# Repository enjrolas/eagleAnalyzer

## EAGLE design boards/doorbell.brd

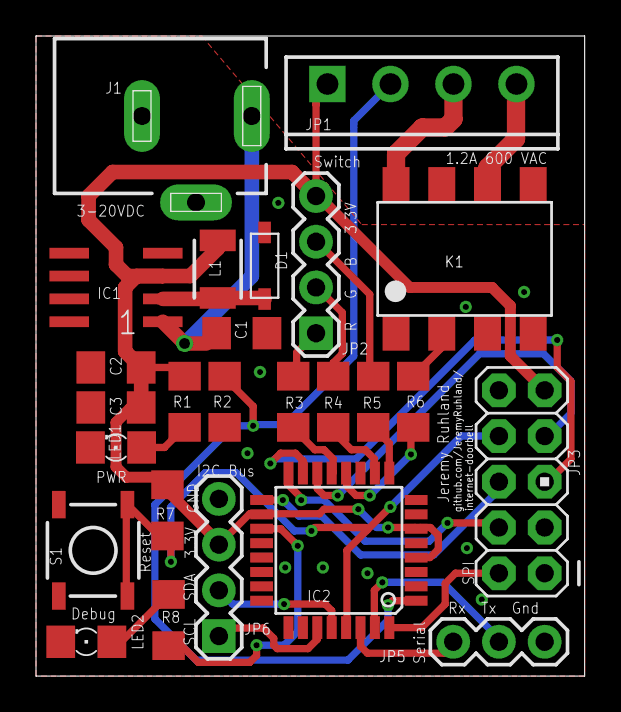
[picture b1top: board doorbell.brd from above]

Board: 2 copper layers, 30.5 x 35.6 mm, 25 parts (0 on the bottom side), 28 nets.

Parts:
C1, C2: 10uf; C1206
C3: 0.1uf; C1206
D1: SOD-123
IC1: AP1509; SOP-8
IC2: MEGA8-AI; TQFP32-08
J1: DCJ0202SILK; DCJ0202_SILK
JP1: SCREWTERMINAL-3.5MM-4_SILK
JP2: LED_header; 1X04
JP3: M05X2PTH; AVR_ICSP
JP5: 1X03
JP6: 1X04
K1: AQH213B; DIL08SMD
L1: 47uh; 1210
LED1, LED2: 1206
R1, R3, R4, R5, R6, R8: 160; R1206
R2, R7: 10k; R1206
S1: TACTILE_SWITCH_SMD

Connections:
3.3V: C2.1, C3.1, IC1.3, IC2.4, IC2.6, IC2.18, JP1.1, JP2.4, JP3.9, JP6.3, L1.2, R1.2, R7.2
B: IC2.13, R3.1
BELL: IC2.12, R6.2
BELL+: JP1.3, K1.8
BELL-: JP1.4, K1.6
CS: IC2.14, JP3.7
DBG: IC2.19, R8.2
G: IC2.10, R4.1
GND: C1.2, C2.2, C3.2, D1.A, IC1.4, IC1.5, IC1.6, IC1.7, IC1.8, IC2.3, IC2.5, IC2.21, J1.2, J1.3, JP3.10, JP5.3, JP6.4, K1.4, LED1.C, LED2.C, R2.1, S1.1, S1.2
INT0: IC2.32, JP3.2
MISO: IC2.16, JP3.4
MOSI: IC2.15, JP3.5
unnamed: K1.2, R6.1
unnamed: C1.1, IC1.1, J1.1
unnamed: D1.C, IC1.2, L1.1
unnamed: IC2.27, JP6.1
unnamed: IC2.28, JP6.2
unnamed: LED1.A, R1.1
unnamed: LED2.A, R8.1
unnamed: JP2.3, R5.2
unnamed: JP2.2, R4.2
unnamed: JP2.1, R3.2
R: IC2.9, R5.1
RST: IC2.29, JP3.8, R7.1, S1.3, S1.4
RX: IC2.30, JP5.1
SCK: IC2.17, JP3.6
SIG: IC2.1, JP1.2, R2.2
TX: IC2.31, JP5.2

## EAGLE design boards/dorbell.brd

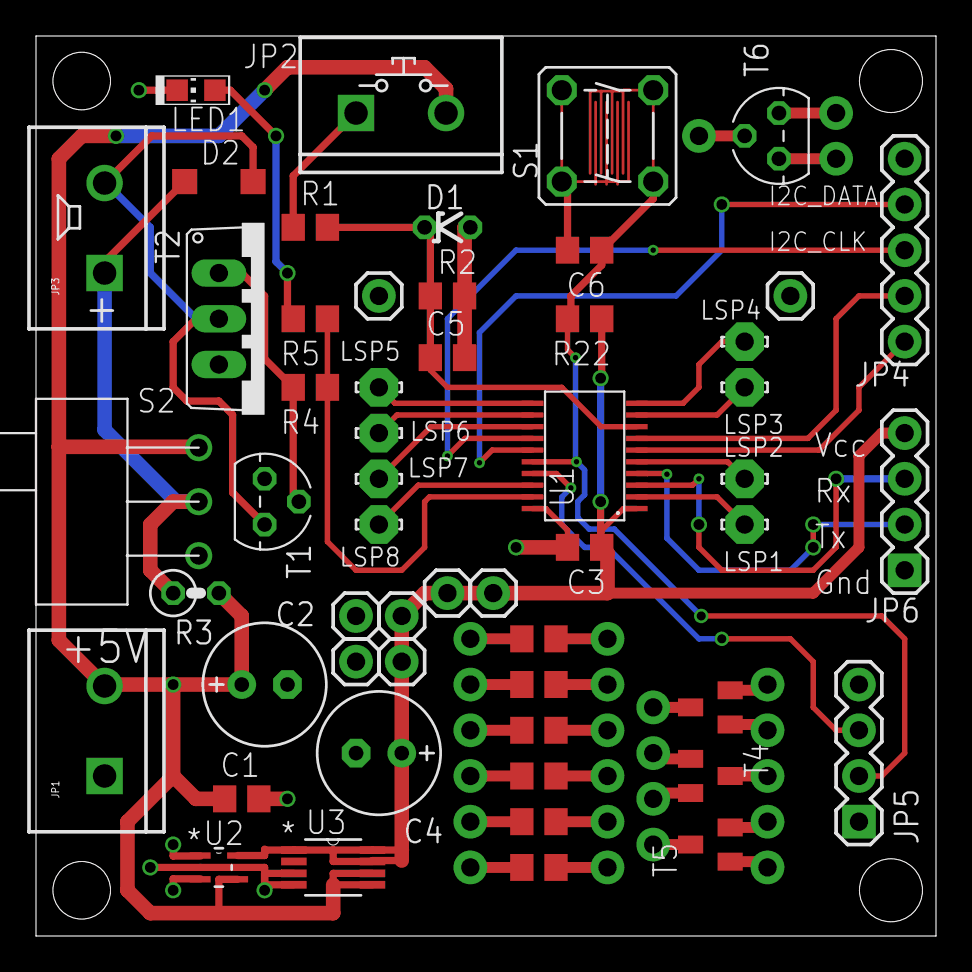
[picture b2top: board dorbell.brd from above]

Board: 2 copper layers, 50.0 x 50.0 mm, 78 parts (0 on the bottom side), 50 nets.

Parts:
C1, C3, C5, C6: C0805
C2, C4: E2,5-7
D1: 3.3V; ZDIO-2.5
D2: 1N4148; SOD123
JP1, JP2, JP3: T1; SCREWTERMINAL-5MM-2
JP4: 1X05
JP5, JP6: 1X04
JP7, JP8, JP9, JP10, JP11, JP12, JP13, JP14, JP15, JP16, JP17, JP18, JP19, JP20, JP21, JP22, JP23, JP24, JP25, JP26, JP27, JP28, JP29, JP30: M01SMDNS; 1X01NS
JP31, JP32, JP33, JP34, JP35, JP36, JP37, JP38: M01PTH; 1X01
LED1: GREEN; CHIP-LED0805
LSP1, LSP2, LSP3, LSP4, LSP5, LSP6, LSP7, LSP8: LSP10
R1, R4, R5: 470; R0805
R2, R6, R7, R8, R9, R10, R11: 4.7K; R0805
R3: 4.7K; 0207/2V
R22: 47K; R0805
S1: DTE6
S2: SWITCH_2DIR; SWITCH_SLIDE
T1: 2N3904; TO92
T2: BD537; TO220V
T3, T4, T5: SOT23-BEC
T6: TO92-E1
U1: G2XX3---PW20; PW20
U2: TPS71533_DCK_5; DCK5
U3: TPS77333; DGK8

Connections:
+5V: C1.1, C2.+, JP1.2, JP2.2, R3.2, S2.P$1, U2.4, U3.5, U3.6
BTN: C5.1, D1.C, R1.2, R2.2, U1.8
GND: C1.2, C2.-, C3.2, C4.-, C5.2, C6.2, D1.A, JP1.1, JP4.1, JP5.1, JP6.1, JP31.1, JP32.1, JP33.1, JP34.1, LED1.C, R2.1, S1.1, S1.2, T1.3, T2.3, U1.20, U2.2, U3.3, U3.4
I2C_CLK: JP4.3, U1.14
I2C_DATA: JP4.2, U1.15
unnamed: D2.A, JP3.2, T1.1, T2.2
unnamed: D2.C, JP3.1, R3.1, S2.P$2
unnamed: R4.2, T1.2, T2.1
unnamed: JP2.1, R1.1
unnamed: LED1.A, R5.2
unnamed: JP7.1, R6.2
unnamed: JP8.1, R6.1
unnamed: JP9.1, R7.2
unnamed: JP10.1, R7.1
unnamed: JP11.1, R8.2
unnamed: JP12.1, R8.1
unnamed: JP13.1, R9.2
unnamed: JP14.1, R9.1
unnamed: JP15.1, R10.2
unnamed: JP16.1, R10.1
unnamed: JP17.1, R11.2
unnamed: JP18.1, R11.1
unnamed: JP19.1, T3.B
unnamed: JP20.1, T3.C
unnamed: JP21.1, T3.E
unnamed: JP22.1, T4.B
unnamed: JP23.1, T4.C
unnamed: JP24.1, T4.E
unnamed: JP25.1, T5.B
unnamed: JP26.1, T5.C
unnamed: JP27.1, T5.E
unnamed: JP28.1, T6.2
unnamed: JP29.1, T6.1
unnamed: JP30.1, T6.3
P1.0: LSP1.MP, U1.2
P1.3: LSP2.MP, U1.5
P2.1: LSP3.MP, U1.9
P2.2: LSP4.MP, U1.10
P2.3: LSP5.MP, U1.11
P2.4: LSP6.MP, U1.12
P2.5: LSP7.MP, U1.13
P2.7: LSP8.MP, U1.18
PWM: R4.1, R5.1, U1.19
RST: C6.1, JP5.2, R22.1, S1.3, S1.4, U1.16
RXD: JP6.3, U1.3
TEST: JP5.3, U1.17
TXD: JP6.2, U1.4
UCB0CLK: JP4.4, U1.7
UCB0STE: JP4.5, U1.6
VCC: C3.1, C4.+, JP6.4, JP35.1, JP36.1, JP37.1, JP38.1, R22.2, U1.1, U2.5, U3.1, U3.7, U3.8

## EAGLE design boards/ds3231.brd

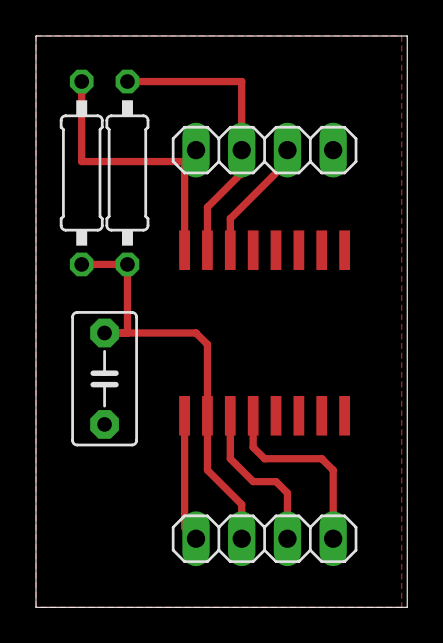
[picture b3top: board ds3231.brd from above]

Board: 2 copper layers, 20.6 x 31.7 mm, 6 parts (0 on the bottom side), 8 nets.

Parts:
C1: C5B3.5
IC1: DS3231SN; SO16W
JP1, JP2: 1X04
R1, R2: 0207/10

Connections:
GND: C1.2, IC1.5, IC1.6, IC1.7, IC1.8, IC1.9, IC1.10, IC1.11, IC1.12, IC1.13, JP1.4
unnamed: C1.1, IC1.2, JP2.2, R1.2, R2.2
unnamed: IC1.1, JP2.1
unnamed: IC1.14, JP1.3
unnamed: IC1.4, JP2.4
unnamed: IC1.3, JP2.3
unnamed: IC1.15, JP1.2, R2.1
R1: IC1.16, JP1.1, R1.1

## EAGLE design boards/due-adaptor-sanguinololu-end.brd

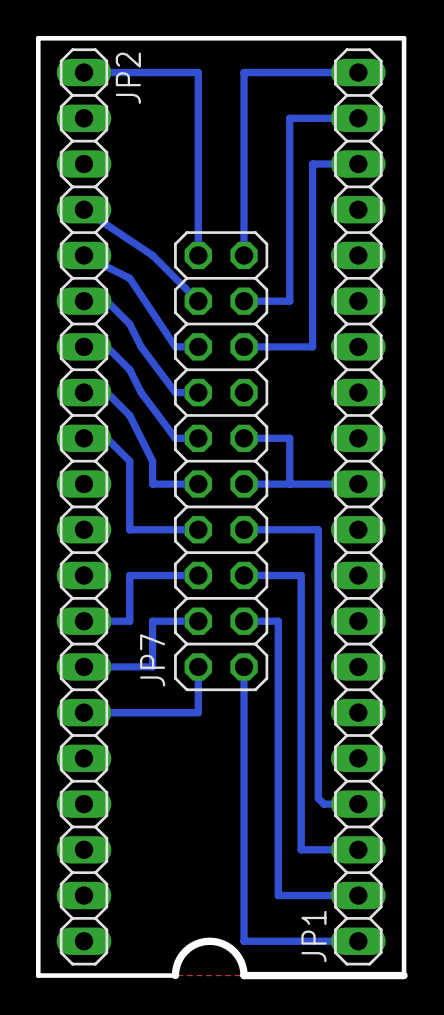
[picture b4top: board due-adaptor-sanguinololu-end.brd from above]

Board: 2 copper layers, 20.3 x 52.1 mm, 3 parts (0 on the bottom side), 18 nets.

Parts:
JP1, JP2: 1X20
JP7: 2X10

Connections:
unnamed: JP1.11, JP7.9, JP7.11
PWM03_XSTOP: JP2.4, JP7.18
RX2_D17_ZSTOP: JP2.6, JP7.14
RX4_D14_YSTOP: JP2.5, JP7.16
S_BED_H: JP1.18, JP7.15
S_BED_T: JP2.14, JP7.4
S_EDIR: JP1.1, JP7.1
S_ESTEP: JP1.2, JP7.3
S_E_H: JP1.19, JP7.17
S_E_T: JP2.13, JP7.6
S_XDIR: JP2.7, JP7.12
S_XSTEP: JP2.1, JP7.20
S_XYE_EN: JP1.20, JP7.19
S_YDIR: JP2.9, JP7.8
S_YSTEP: JP2.8, JP7.10
S_ZDIR: JP1.3, JP7.5
S_ZSTEP: JP1.4, JP7.7
S_Z_EN: JP2.15, JP7.2

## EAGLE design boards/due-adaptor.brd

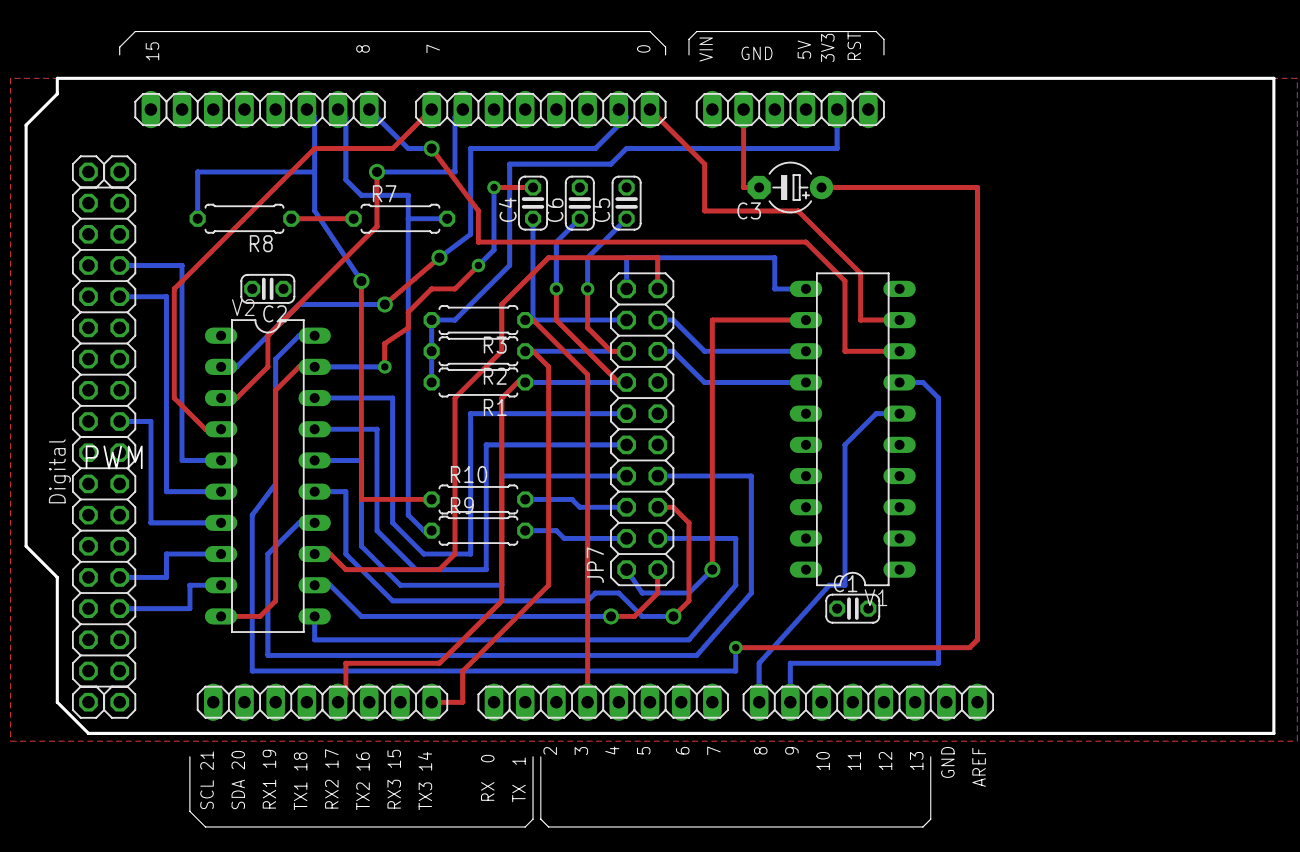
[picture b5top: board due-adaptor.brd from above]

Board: 2 copper layers, 101.6 x 53.3 mm, 28 parts (0 on the bottom side), 34 nets.

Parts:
ADC(H): 1X08
ADCL: 1X08
C1, C2, C4, C5, C6: 0.1uF; C025-024X044
C3: 100uF; E5-4
COMMUNICATION: 1X08
JP1, JP2: Digital; 2X08
JP3, JP4, JP5, JP6: 1X01
JP7: 2X10
POWER: 1X06
PWM(H): 1X08
PWM(L): 1X08
R1, R2, R3: 47K; 0207/7
R7, R8: 150K; 0207/7
R9, R10: 100K; 0207/7
V1, V2: 74HCT541N; DIL20

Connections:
+3V3: POWER.2, R1.2, R2.2, R3.2
+5V: C1.1, C2.1, C3.+, JP3.1, JP4.1, POWER.3, V1.20, V2.20
ADC0_XSTEP: ADCL.1, V1.9
ADC1_XDIR: ADCL.2, V2.2
ADC6_YSTEP: ADCL.7, V2.3
ADC7_YDIR: ADCL.8, V2.4
ADC8_Z_EN: ADC(H).1, V1.8
ADC9_BED_T: ADC(H).2, R7.2, R9.1
ADC10_E_T: ADC(H).3, R8.2, R10.1
DIG26_ESTEP: JP1.12, V2.9
DIG28_EDIR: JP1.10, V2.8
DIG38_XYE_EN: JP2.16, V2.7
DIG46_ZSTEP: JP2.8, V2.6
DIG48_ZDIR: JP2.6, V2.5
GND: C1.2, C2.2, C3.-, C4.2, C5.2, C6.2, JP5.1, JP6.1, JP7.9, JP7.11, POWER.4, POWER.5, PWM(H).7, R7.1, R8.1, V1.1, V1.10, V1.19, V2.1, V2.10, V2.19
PWM03_XSTOP: C4.1, JP7.18, PWM(L).4, R3.1
PWM08_BED_H: PWM(H).1, V1.6
PWM09_E_H: PWM(H).2, V1.7
RX2_D17_ZSTOP: C6.1, COMMUNICATION.5, JP7.14, R1.1
RX4_D14_YSTOP: C5.1, COMMUNICATION.8, JP7.16, R2.1
S_BED_H: JP7.15, V1.14
S_BED_T: JP7.4, R9.2
S_EDIR: JP7.1, V2.12
S_ESTEP: JP7.3, V2.11
S_E_H: JP7.17, V1.13
S_E_T: JP7.6, R10.2
S_XDIR: JP7.12, V2.18
S_XSTEP: JP7.20, V1.11
S_XYE_EN: JP7.19, V2.13
S_YDIR: JP7.8, V2.16
S_YSTEP: JP7.10, V2.17
S_ZDIR: JP7.5, V2.15
S_ZSTEP: JP7.7, V2.14
S_Z_EN: JP7.2, V1.12

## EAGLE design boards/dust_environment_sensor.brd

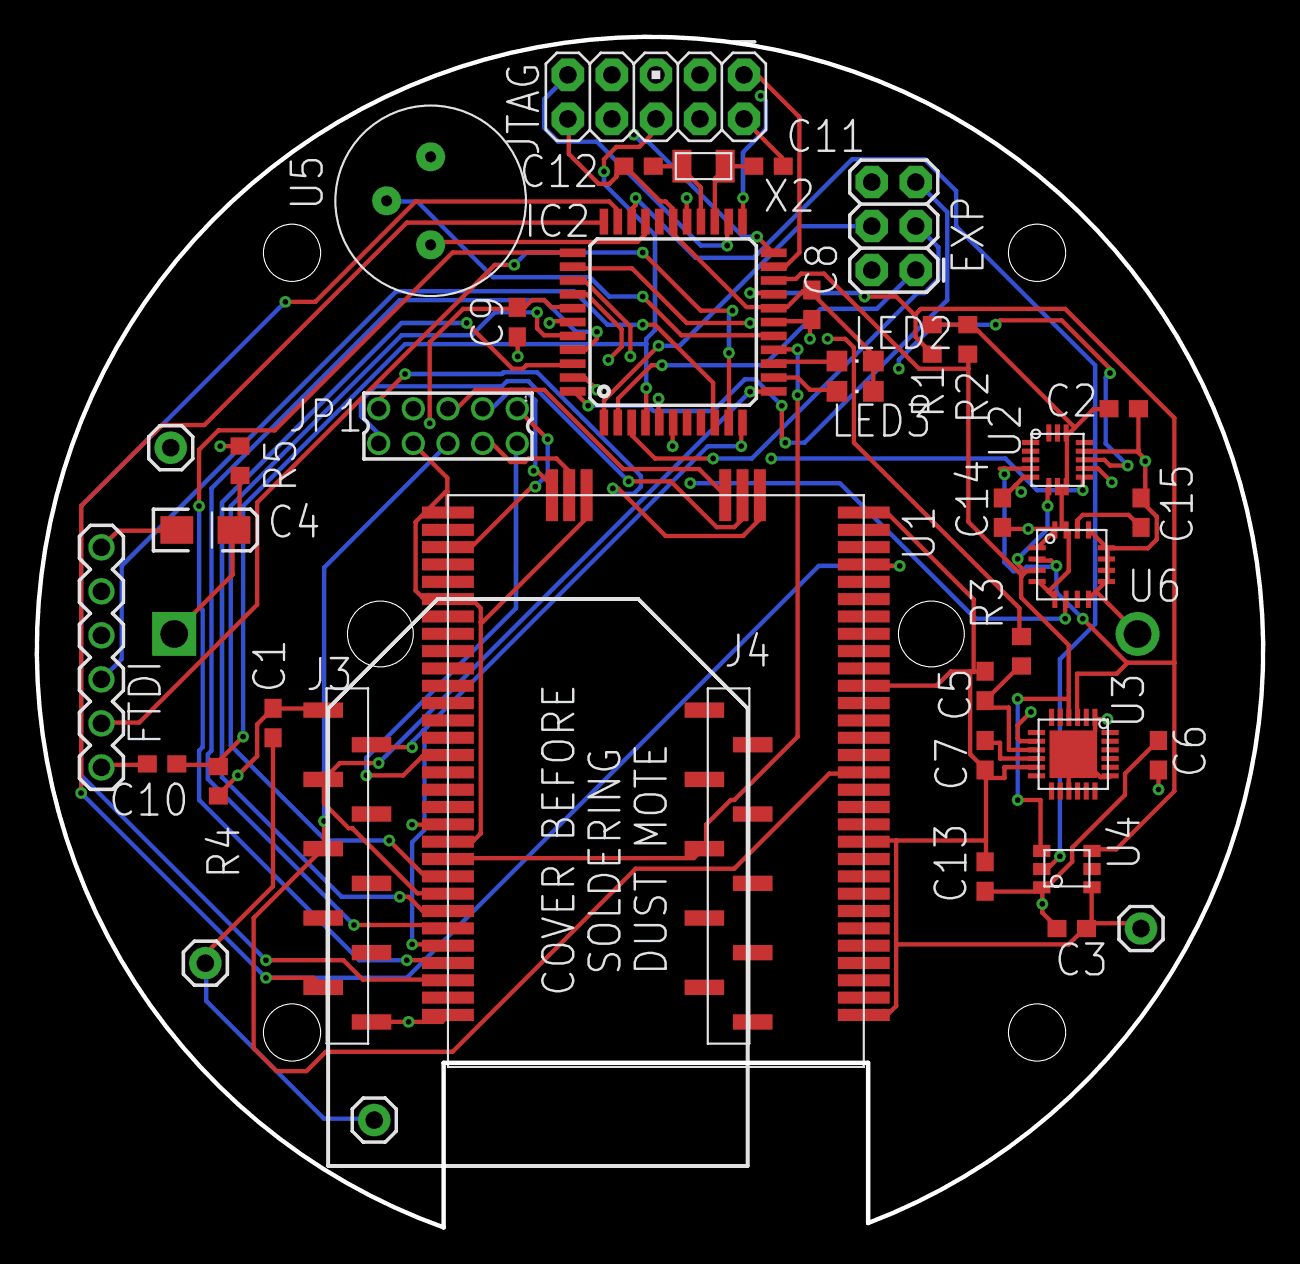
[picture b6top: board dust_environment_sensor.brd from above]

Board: 4 copper layers, 70.8 x 68.7 mm, 45 parts (1 on the bottom side), 48 nets.

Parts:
C1, C3, C5, C6, C8, C9, C10, C13, C15: 100n; C0603
C2, C14: 10u; C0603
C4: 100u; EIA3216-KIT
C7: 4.7u; C0603
C11, C12: 10p; C0603
IC2: ATMEGA644A; TQFP44
J1: 3.6V Lithium C cell; BX0036
J2: EXP; 2X3
J3: XBEE_1-10SMT; XBEE_1-10_SMT
J4: XBEE_11-20SMT; XBEE_11-20_SMT
JP1: 87758-1016
JP4, JP5, JP6, JP7: M01PTH; 1X01
JP8: 1X06
JP9: JTAG; AVR_ICSP
LED2, LED3: CHIPLED_0805
R1, R2: 2.2k; R0603
R3: 15; R0603
R4: 10k; R0603
R5: 0R; R0603
STANDOFF1, STANDOFF2, STANDOFF3, STANDOFF4: STAND-OFF
U1: LTP5901; LTP5901_MODULE
U2: LIS3DH; LGA16_ST
U3: SI7005; QFN24_SILICON_LABS
U4: TSL2560; CL6_TAOS
U5: AMN41121
U6: L3GD20; LGA16_4X4_ST
X2: 32.768KHz; ABS07

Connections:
ACCEL_INT1: IC2.37, U2.11
ACCEL_INT2: IC2.36, U2.9
ATMEGA_TO_FTDI: IC2.10, JP8.5
EXP_CSN: IC2.44, J2.5
EXP_MISO: IC2.2, J2.1
EXP_MOSI: IC2.1, J2.4
EXP_SCK: IC2.3, J2.3
FLASH_P_ENN: JP1.2, U1.51
FTDI_TO_ATMEGA: IC2.9, JP8.4
GND: C1.2, C2.2, C3.2, C4.C, C5.2, C6.2, C7.2, C8.1, C9.1, C11.2, C12.2, C13.2, C14.2, C15.2, IC2.6, IC2.18, IC2.28, IC2.39, J1.NEG, J2.6, J3.10, JP1.8, JP4.1, JP5.1, JP6.1, JP7.1, JP8.1, JP8.2, JP9.2, JP9.10, LED2.C, LED3.C, U1.1, U1.11, U1.20, U1.30, U1.34, U1.37, U1.42, U1.56, U1.66, U2.5, U2.10, U2.12, U3.1, U3.8, U3.11, U3.15, U3.19, U3.PAD, U4.2, U5.GND, U6.8, U6.9, U6.10, U6.11, U6.12, U6.13
GYRO_INT2: IC2.43, U6.6
HUMID_VCC: IC2.35, R3.2
I2C_SCL: IC2.19, R1.1, U2.4, U3.3, U4.4, U6.2
I2C_SDA: IC2.20, R2.1, U2.6, U3.4, U4.5, U6.3
IPCS_MISO: JP1.5, U1.33
IPCS_MOSI: JP1.4, U1.35
IPCS_SCK: JP1.3, U1.36
IPCS_SSN: JP1.1, U1.39
LED1: IC2.14, LED2.A
LED2: IC2.13, LED3.A
LIGHT_INT: IC2.31, U4.6
MOTE_API_RX: IC2.12, J3.3, U1.59
MOTE_API_TX: IC2.11, J3.2, U1.62
MOTE_CLI_RX: JP1.10, U1.32
MOTE_CLI_TX: JP1.9, U1.31
MOTE_RADIO_INHIBIT: IC2.32, U1.64
MOTE_RESETN: J3.5, JP1.6, U1.15
MOTE_RX_CTSN: IC2.40, U1.58
MOTE_RX_RTSN: IC2.15, J4.16, U1.57
MOTE_SLEEPN: IC2.33, J3.9, U1.27
MOTE_TIMEN: IC2.34, U1.63
MOTE_TX_CTSN: IC2.41, U1.61
MOTE_TX_RTSN: IC2.42, U1.60
unnamed: C7.1, U3.10
unnamed: C15.1, U6.14
unnamed: C5.1, R3.1, U3.9
unnamed: C11.1, IC2.25, X2.2
unnamed: C12.1, IC2.26, X2.1
PIR_OUT: IC2.16, U5.OUT
PIR_VCC: IC2.30, U5.VDD
RST: C10.1, IC2.4, JP9.6, R4.1
RTS#: C10.2, JP8.6
TCK: IC2.21, JP9.1
TDI: IC2.24, JP9.9
TDO: IC2.23, JP9.3
TMS: IC2.22, JP9.5
VBATT: C4.A, J1.POS, R5.2
VCC: C1.1, C2.1, C3.1, C6.1, C8.2, C9.2, C13.1, C14.1, IC2.5, IC2.17, IC2.27, IC2.38, J2.2, J3.1, JP1.7, JP9.4, R1.2, R2.2, R4.2, R5.1, U1.55, U2.7, U2.8, U2.14, U4.1, U6.1, U6.4, U6.5, U6.15, U6.16

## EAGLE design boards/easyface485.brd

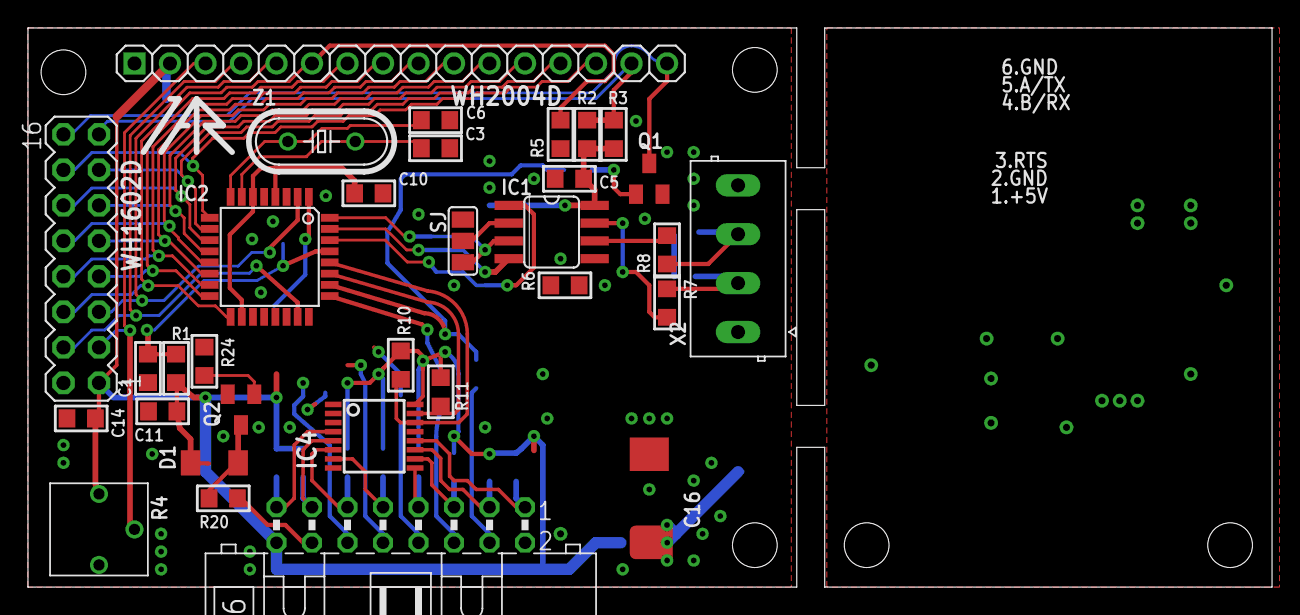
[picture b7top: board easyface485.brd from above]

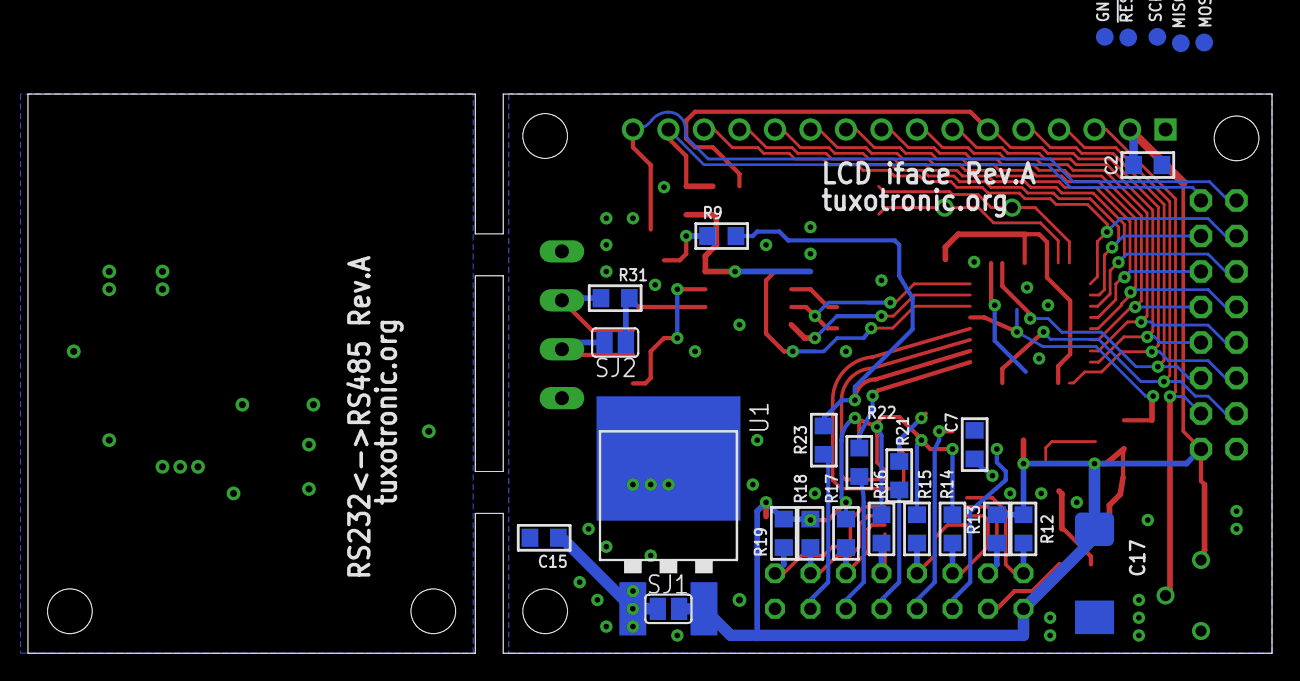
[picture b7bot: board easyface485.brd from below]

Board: 2 copper layers, 89.0 x 40.0 mm, 58 parts (25 on the bottom side), 53 nets.

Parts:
!RESET: TPB1,27; B1,27
C1, C2, C5, C7, C10, C11, C14, C15: 0.1; C0805
C3, C6: 22pF; C0805
C16: 100uF/16V; SMC_D
C17: 220uF/6V3; SMC_D
D1: SOD80
GND: TPB1,27; B1,27
IC1: MAX487-S; SO08
IC2: ATMEGA88-16AU; TQFP32-08
IC4: PCA9534PW; SSOP16
MISO: TPB1,27; B1,27
MOSI: TPB1,27; B1,27
Q1, Q2: MMBT2222; SOT23
R1, R6: 10K; R0805
R2, R3, R7, R8: 10; R0805
R4: RTRIM-3362P
R5, R10, R11, R12, R13, R14, R15, R16, R17, R18, R19: 4.7K; R0805
R9, R24: 1K; R0805
R20, R21, R22, R23: 0; R0805
R31: 120; R0805
SCK: TPB1,27; B1,27
SJ: SJ_2
SJ1, SJ2: SJ
SV: ML16L
U1: L7805D2TT; D2PAK
U$: LOGO; TT_LOGO
WH1602D: MA08-2
WH2004D: 1X16RND
X2: DG3XX-04-3.5; DG350-3.5-04P
Z1: 14,7456 MHz; HC49/S

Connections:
!RESET: !RESET.PP, C1.2, IC2.29, R1.1
+5V: C2.1, C5.1, C10.1, C11.1, C14.1, C17.+, D1.C, IC1.8, IC2.4, IC2.6, IC2.18, IC4.16, R1.2, R2.1, R3.1, R4.1, R10.2, R11.2, R12.2, R13.2, R14.2, R15.2, R16.2, R17.2, R18.2, R19.2, SJ1.2, SV.16, U1.3, WH1602D.1, WH2004D.2
ADC6: IC2.19, SV.12
ADC7: IC2.22, SV.10
BL-A: R2.2, R3.2, WH1602D.15, WH2004D.15
BL-K: Q1.3, WH1602D.16, WH2004D.16
BUZZER: IC2.1, R24.1
DB0: IC2.16, MISO.PP, WH1602D.7, WH2004D.7
DB1: IC2.15, MOSI.PP, WH1602D.8, WH2004D.8
DB2: IC2.14, WH1602D.9, WH2004D.9
DB3: IC2.13, WH1602D.10, WH2004D.10
DB4: IC2.12, WH1602D.11, WH2004D.11
DB5: IC2.11, WH1602D.12, WH2004D.12
DB6: IC2.10, WH1602D.13, WH2004D.13
DB7: IC2.9, WH1602D.14, WH2004D.14
DE: IC1.3, IC2.32, R6.2, SJ.1
E: IC2.17, R5.2, SCK.PP, WH1602D.6, WH2004D.6
GND: C1.1, C2.2, C3.1, C5.2, C6.1, C7.2, C10.2, C11.2, C14.2, C15.2, C16.-, C17.-, GND.PP, IC1.5, IC2.3, IC2.5, IC2.21, IC4.1, IC4.2, IC4.3, IC4.8, Q1.2, Q2.2, R4.3, R5.1, R6.1, SJ.3, SV.2, U1.2, WH1602D.2, WH2004D.1, X2.4
LIGHT: IC2.26, R9.1, R23.1
unnamed: R7.1, SJ2.2, X2.2
unnamed: IC4.4, R12.1, SV.15
unnamed: C7.1, IC2.20
unnamed: IC1.2, SJ.2
unnamed: IC4.5, R13.1, SV.13
unnamed: Q2.1, R24.2
unnamed: IC4.6, R14.1, SV.11
unnamed: R20.2, SV.14
unnamed: D1.A, Q2.3, R20.1
unnamed: IC4.7, R15.1, SV.9
unnamed: Q1.1, R9.2
unnamed: IC4.9, R16.1, SV.7
unnamed: IC4.10, R17.1, SV.5
unnamed: IC4.11, R18.1, SV.3
unnamed: IC4.12, R19.1, SV.1
unnamed: C3.2, IC2.7, Z1.2
unnamed: R8.1, R31.1, X2.3
unnamed: R21.2, SV.8
unnamed: R22.2, SV.6
unnamed: R23.2, SV.4
unnamed: R31.2, SJ2.1
unnamed: IC1.6, R8.2
unnamed: IC1.7, R7.2
PC1: IC2.24, R21.1
PC2: IC2.25, R22.1
RS: IC2.23, WH1602D.4, WH2004D.4
RW: IC2.2, WH1602D.5, WH2004D.5
RXD: IC1.1, IC2.30
SCL: IC2.28, IC4.14, R10.1
SDA: IC2.27, IC4.15, R11.1
TXD: IC1.4, IC2.31
VDD: C15.1, C16.+, SJ1.1, U1.1, X2.1
VO: R4.2, WH1602D.3, WH2004D.3
XTAL2: C6.2, IC2.8, Z1.1

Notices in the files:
boards/due-adaptor.brd:
Licence: GPL
parts and their libraries:
sparkfun: Licensing: CC v3.0 Share-Alike You are welcome to use this library for commercial purposes.
